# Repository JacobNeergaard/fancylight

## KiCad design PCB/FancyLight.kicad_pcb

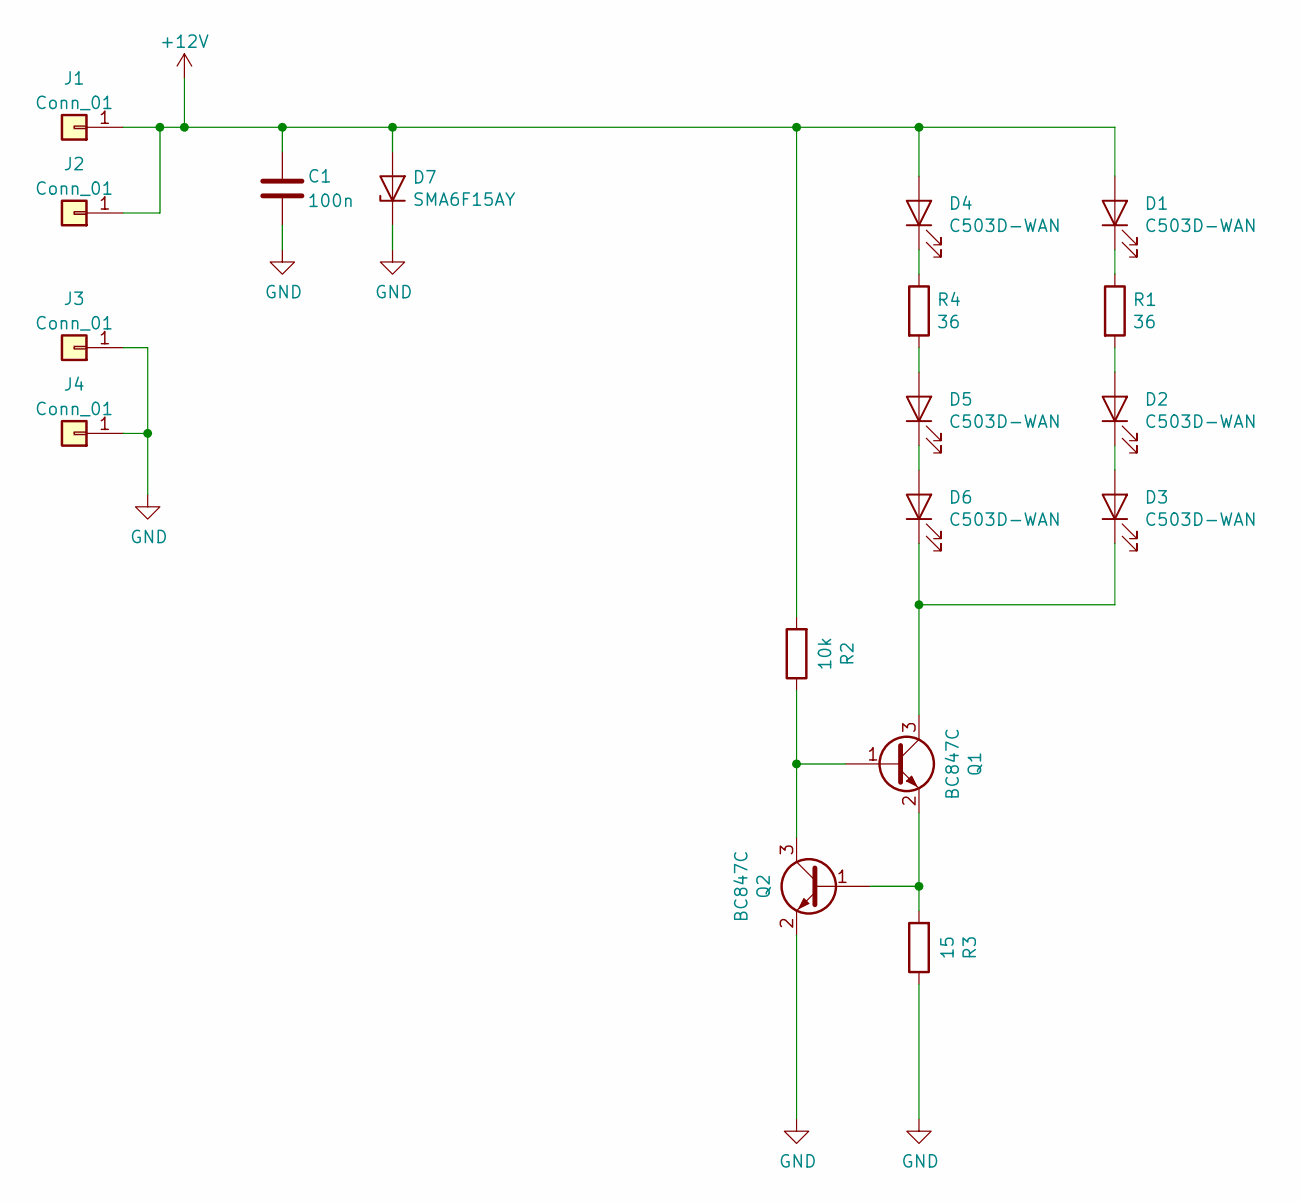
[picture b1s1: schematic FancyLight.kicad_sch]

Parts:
C1: 100n; C_0805_2012Metric
D1, D2, D3, D4, D5, D6: C503D-WAN; LED_D5.0mm
D7: SMA6F15AY; D_SMA
J1, J2, J3, J4: Conn_01; ThruHole1mm_1.6Pad
Q1, Q2: BC847C; SOT-23
R1, R4: 36; R_0805_2012Metric
R2: 10k; R_0805_2012Metric
R3: 15; R_0805_2012Metric

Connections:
+12V: C1.1, D1.2 (A), D4.2 (A), D7.2 (A), J1.1, J2.1, R2.2
GND: C1.2, D7.1 (K), J3.1, J4.1, Q2.2 (E), R3.1
unnamed: D1.1 (K), R1.1
unnamed: D2.2 (A), R1.2
unnamed: D2.1 (K), D3.2 (A)
unnamed: D3.1 (K), D6.1 (K), Q1.3 (C)
unnamed: D4.1 (K), R4.1
unnamed: D5.2 (A), R4.2
unnamed: D5.1 (K), D6.2 (A)
unnamed: Q1.1 (B), Q2.3 (C), R2.1
unnamed: Q1.2 (E), Q2.1 (B), R3.2

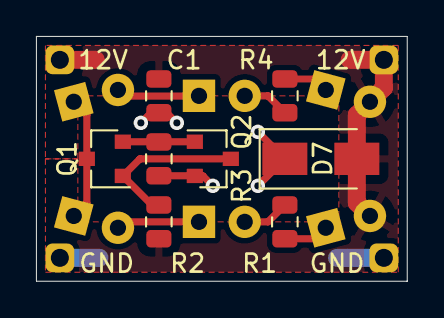
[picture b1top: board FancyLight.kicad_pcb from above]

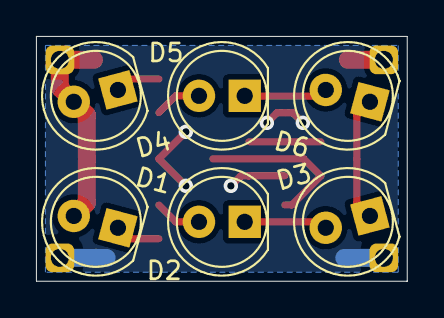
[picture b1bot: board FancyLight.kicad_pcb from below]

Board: 2 copper layers, 20.6 x 13.6 mm, 18 parts (6 on the bottom side), 11 nets.

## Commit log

2023-03-05 First PCB

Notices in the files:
PCB/FancyLight.kicad_pcb:
Apache License 2.0
